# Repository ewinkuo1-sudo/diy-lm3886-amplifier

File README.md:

# LM3886 DIY AB 類立體聲後級

用兩顆 LM3886T 製作**內建電源的雙聲道純後級**，搭配使用者現有的 **Eversolo DAC-Z10（DAC＋前級）**。訊號路徑為 **DAC-Z10 RCA 前級輸出 → 本後級 → 喇叭**，音量與訊源選擇由 Z10 負責。本機採固定增益，前面板規劃電源及狀態指示。

這是第三個獨立擴大機專案，可與 [TPA3255 練習機](https://github.com/ewinkuo1-sudo/diy-tpa3255-amplifier) 及 [Purifi 主力機](https://github.com/ewinkuo1-sudo/diy-purifi-amplifier) 比較架構與製作經驗。

## 目前狀態（2026-10-01 深夜）

- **方向改為「先挑殼、散熱器放殼內、以現有零件重排 PCB＝V0.6」**。機殼改選台灣現貨 **弘宙 102**（型錄 b420 前面板寬、d395 機身寬、c285 深不含把手、e105 高 → 內尺寸估 **393×273×100**，賣家未確認；BZ4312A2 留給下一台）。配置：後排「放大板 L｜電源板｜放大板 R」、前排變壓器居中、左前控制板、右前市電板；散熱器 **150×90×30 鋁擠 ×2 內置兩側**（鰭片朝牆、底板朝板、上蓋底板開通風孔；規格依 8 Ω 連續正弦 θSA ≤1.2 °C/W）。3D 配置：[chassis_102_v06_3d.png](docs/diagrams/chassis_102_v06_3d.png)。下單前問賣家內寬、通風孔、後面板是否空白。
- **2026-10-25 3D 列印機殼 v0.2**：列印機確定為 Bambu Lab H2D，改成底殼一體（298×313×81，內深 305）＋上蓋一片＋市電護罩＋機腳，配置換成兩片現成板（蝦皮 UPC1237 保護器、AC110V 軟啟動板，使用者暫定買）；剛性用格狀梁估算，底板變壓器區肋加高、上蓋肋 13 mm／40 mm 間距後全部過關，散熱片螺絲要墊鋁條。見 [docs/16](docs/16-3D列印機殼v0.2.md)。**未切片、未試印、全是估算。**
- **2026-10-25 另起 3D 列印機殼候選（v0.1）**：使用者買了 176×33×60 散熱片 ×?（蝦皮），評估與模型在 [docs/15](docs/15-3D列印機殼方案.md)：散熱片當左右側牆外露、四周框拆 6 件列印（≤216 mm）、上下蓋建議 2 mm 鋁板；θSA 估約 1.2 °C/W 與原要求同級；材料要 PETG／ASA。**未定案**，弘宙 102 方案照舊保留；圖 `docs/diagrams/chassis_print_v01_*.png`，模型 `mechanical/chassis-print-v01/`。
- **控制／保護板 CTRL 與市電板 MAINS 第一版原理圖＋PCB V0.6 已畫**（2026-10-01 深夜）：CTRL 70×120（UPC1237 保護、7812 輔助電源、G2RL-1-E 喇叭繼電器 ×2、SFH617A 光耦靜音、TL431 旁通計時）、MAINS 70×100（SL22 10005 NTC、K_BYP、K_TRIG）。ERC 0、DRC 0 錯誤，市電／低壓銅箔距離 7.25 mm。繼電器 DC 分斷取 30 VDC 等級（使用者接受）。見 [docs/14](docs/14-V0.4-控制與保護板設計草案.md) 狀態列、[pcb/README「PCB V0.6」](pcb/README.md)。
- **放大板與電源板 V0.6 也畫了（2026-10-02 凌晨，以型錄幾何先畫）**：放大板 **90×80**，U1 用 KiCad 函式庫 TO-220-11 直立封裝、背板貼板邊直接鎖散熱器；電源板 **92×120**，兩欄 381LX、GBJ 朝前、AC 端子朝變壓器、DC 端子朝放大板（snubber 預留位未上板）。**V0.6 五板皆 DRC 0 錯誤**，機箱 3D 已換成真板。IC 幾何、C2 腳距、繼電器腳位到貨要核對。詳見 [pcb/README](pcb/README.md)；V0.5.1／V0.5／V0.4／V0.3 為歷史。**全部仍是工程草稿，不可送製。**
- **放大板與電源板現行為 V0.6.1（2026-10-03 使用者選定併入 main）**：零件、擺位、板尺寸、機殼與散熱器配置與 V0.6 完全相同，只把載流走線加寬到間距規則與鄰近焊盤允許的上限（放大板負電源腳間線 0.5→0.9、電源板主幹 3→5 等），兩板 DRC 0；V0.6 vs V0.6.1 走線電阻對照見 [pcb/README「PCB V0.6.1」](pcb/README.md)。CTRL／MAINS 仍為 V0.6 板檔。
- **目標喇叭 Usher Be-718**（標稱 8 Ω、實測低中音 >6 Ω、約 85 dB）：匹配估算見 [docs/01](docs/01-設計規格.md)；功率／散熱討論以 6–8 Ω 為準。
- **已到貨**：環形變壓器、yosontw 40 件電阻／WIMA／CDE／ROE（2026-09-22）、LM3886T 拆機品 ×4（2026-09-29，T 封裝、NS 打標）。已付 NT$4,821，整機估 10.9k–16.2k（[採購總表 §5](docs/00-採購總表.md)）。
- **2026-10-01 已量變壓器電氣**（採購總表 §1）：標籤 22V 4.2A×2＋12V 1A ≈ **197 VA**；兩組 22V 空載各 22.29 Vac（DCR 0.25／0.2 Ω）、串接 44.6 Vac 同相；12V 12.27 Vac；一次側約 2 Ω；市電 110 V。最壞軌電壓 **±33.5 V**，帶載推估連續 30–32 W／8 Ω。保險絲提案：一次側 T2.5A（有軟啟動）／T3.15A、22V 各 T5A、12V T1.25A。**未量：帶載電壓、絕緣、溫升。**
- **已量零件尺寸**（2026-09-23）：381LX Ø35×50 腳距 10；EKE Ø12×25 腳距 5；EGW 軸向 40×Ø20（V0.5 起改站立封裝，**腳距 15 是假設待實量**）；變壓器 Ø120×約 50、中心孔 Ø40。
- **選型定案**：C 方案雙聲道、雙橋整流、4×10,000µF／63V；47µF＝ROE EGW 無極性、470µF＝ROE EKE／63V；每聲道 30～40W／8Ω 為探索範圍而非額定。
- **本輪可買**：GBJ2510 ×2＋小散熱片＋M3 件、保險絲、機殼（弘宙 102）、散熱器 150×90×30 ×2、控制板零件一套（G2RL-1-E 12VDC ×5、UPC1237 ×2、SL22 10005、SFH617A-3 ×2、TL431、BC327 ×2、7812 等，見採購總表控制板列）；其餘未購件與順序見採購總表 §2／§3。

**要買零件看 [採購總表](docs/00-採購總表.md)**（已買／未買兩張表＋購買順序）。**要接手看 [HANDOFF.md](HANDOFF.md)**。**歷史逐日紀錄看 [CHANGELOG.md](CHANGELOG.md)**。

## 系統方塊

```mermaid
flowchart LR
    PRE[DAC-Z10\nDAC＋前級／音量控制]
    subgraph AMP[LM3886 純後級機殼]
        IN[RCA 輸入] --> C[兩顆 LM3886T 功率級]
        C --> D[輸出穩定網路]
        D --> REL[喇叭保護／繼電器\nCTRL 板 V0.6 草稿]
        AC[AC 入口／保險絲／開關] --> SS[軟啟動 NTC＋旁通\nMAINS 板 V0.6 草稿]
        SS --> T[隔離環形變壓器]
        T --> PSU[雙橋整流／濾波]
        PSU --> C
        CTRL[UPC1237 啟停／DC 偵測\nCTRL 板 V0.6 草稿] -. 控制 .-> C
        CTRL -. 控制 .-> REL
    end
    PRE --> IN
    REL --> SPK[喇叭]
```

## 設計重點

| 項目 | 目前選擇／待驗證 |
|---|---|
| 功率級 | LM3886T ×2，非橋接、非並聯；已訂拆機品，/NOPB 未確認 |
| 輸出目標 | 每聲道約 30～40W／8Ω 探索範圍，額定待實測 |
| 電源 | 已訂雙 22Vac＋單 12Vac；雙橋架構保留，約 ±30V 等級；VA／電流／最大電壓待確認 |
| 增益 | IC 中頻閉迴路 21 倍；含輸入串阻後約 20.09 倍 |
| 輸入 | DAC-Z10 RCA 前級輸出；後級 40W 約需 0.89Vrms，音量由 Z10 控制 |
| 靜音／保護 | 放大板保留測試跳線；CTRL 板 V0.6 草稿以 UPC1237 做 DC 偵測、開機延遲、掉電快斷，光耦接管 JP1 靜音，解除靜音＝喇叭繼電器吸合 |
| 散熱 | T 封裝，**2026-10-01 改以 8 Ω 連續正弦為準：每聲道散熱器 ≤1.2 °C/W**（6 Ω 正弦需 ≤0.65）、介面 ≤0.3 °C/W；選 150×90×30 鋁擠內置兩側，估法 θSA≈1000／表面積(cm²)；原 0.4 °C/W 是 ±41 V 前提的保守值 |
| 本版負載 | 8Ω 非感性假負載；目標喇叭 Usher Be-718（標稱 8Ω、低中音實測 >6Ω、靈敏度實測約 85dB），匹配估算見 [01](docs/01-設計規格.md)「目標喇叭」節；真實喇叭需另外驗證 |

TI 列出 ±35V、8Ω 下 50W 的元件性能條件；這不是本機實測規格。[原廠資料](https://www.ti.com/product/LM3886)

## 文件

| 文件 | 內容 |
|---|---|
| [採購總表](docs/00-採購總表.md) | **採購單一入口**：已買／未買、購買順序、商品連結 |
| [設計規格](docs/01-設計規格.md) | 電路、接地、Z10 介面與保護邊界 |
| [功率與散熱估算](docs/02-功率與散熱估算.md) | 可重算的數字、公式與假設 |
| [上電與驗收](docs/04-上電與驗收.md) | 從低電壓到雙聲道功率測試 |
| [內建電源與機構](docs/05-內建電源與機構.md) | 變壓器、整流、接地、機殼分區與電源估算 |
| [喇叭保護與啟停設計計畫](docs/13-喇叭保護與啟停設計計畫.md) | V0.4 需求：保護、延遲、DC 偵測與啟停方案 |
| [V0.4 控制與保護板設計草案](docs/14-V0.4-控制與保護板設計草案.md) | 控制板架構、啟停時序、與現有板介面、繼電器篩選、軟啟動與輔助電源計算；開頭狀態列記 2026-10-01 的選型決定與原理圖／PCB V0.6 偏離之處 |
| [控制板原理圖 CTRL](electrical/preview/control-v01.png)／[市電板 MAINS](electrical/preview/mains-v01.png) | 2026-10-01 第一版（生成器 `tools/build_control_board.py`，ERC 0）；[CTRL PDF](electrical/preview/control-v01.pdf)、[MAINS PDF](electrical/preview/mains-v01.pdf) |
| [導讀圖索引](docs/diagrams/README.md) | 單聲道完整接線圖（放大板＋電源板全部畫出）與五張中文導讀圖 |
| [BOM 草案](electrical/bom-draft.csv) | 由 KiCad netlist 匯出，含選型條件 |
| [驗證紀錄](electrical/validation.md) | ERC、網路核對與未驗證事項 |
| [原理圖說明](electrical/README.md) | 放大板與電源次級 KiCad 圖、看圖與重建方式 |
| [PCB](pcb/README.md) | **現行五板：放大板 V0.6.1 90×80 ×2、電源板 V0.6.1 92×120（V0.6 擺位＋加寬走線）、CTRL V0.6 70×120、MAINS V0.6 70×100，皆 DRC 0**；V0.6 放大板／電源板、V0.5.1／V0.5／V0.4／V0.3 歷史：板檔、DRC、審查結論與載流計算表 |
| [機箱 3D 配置](docs/diagrams/chassis_102_v06_3d.png) | 弘宙 102 內部等角＋俯視（`tools/draw_chassis_scene_v06.py`，pyvista；CTRL／MAINS 為真板 3D，放大板與電源板為 V0.6 目標外形示意） |
| [PCB 看圖資料](pcb/inspection-v051/README.md) | V0.5.1（放大板 D＋電源板）正反面銅箔、組裝、3D 預覽與零件核對表；[V0.5](pcb/inspection-v05/README.md)／[V0.4](pcb/inspection-v04/README.md)／[V0.3](pcb/inspection-v03/README.md) 版保留 |
| [工具說明](tools/README.md) | 各腳本用途與執行順序 |
| [接班進度](HANDOFF.md) | 現況與下一階段工作 |
| [變更紀錄](CHANGELOG.md) | 逐日進度歷史 |

## 電路圖與 PCB 預覽

[放大板 PDF](electrical/preview/lm3886-v01.pdf) · [KiCad 原理圖](electrical/lm3886-v01.kicad_sch)

[電源 PDF](electrical/preview/internal-psu-v02.pdf) · [電源 BOM](electrical/psu-bom-draft.csv)

## 重建與下一步

需要 Python 3、KiCad 10 CLI、Poppler 的 `pdftoppm`，Python 無第三方套件需求：

```sh
python3 tools/rebuild.py
```

`rebuild.py` 目前只重建放大板與電源次級原理圖；控制板與市電板（`tools/build_control_board.py`）和所有 PCB 腳本要手動跑，順序見 [tools/README](tools/README.md)。

下一步（詳見 [HANDOFF](HANDOFF.md)）：量 LM3886T 三個尺寸、問賣家弘宙 102 內寬 → 必要時修正 V0.6.1 放大板的 U1 位置；審控制板原理圖與 PCB、買控制板零件並核對繼電器腳位；麵包板實測 UPC1237 在 12 V 供電下的門檻與延遲；變壓器帶載量測。放大板單獨驗證時仍可用限流實驗電源；成機供電採內建方案。

PDF 重製：先執行 `python3 tools/rebuild.py`，再以安裝 reportlab／pypdf 的 Python 執行 `tools/build_project_pdf.py`；非 Windows 環境需設定 `LM3886_FONT` 指向 CJK TrueType 字型。產物在 `output/`，不入版控。

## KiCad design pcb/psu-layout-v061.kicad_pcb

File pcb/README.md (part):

# PCB

**現行版本：放大板與電源板 V0.6.1（2026-10-03 使用者選定併入 main，V0.6 擺位不動、載流走線加寬，見「PCB V0.6.1」節），CTRL／MAINS V0.6。** V0.6 放大板／電源板自同日起為歷史（板檔保留）。**V0.5.1 自 2026-10-02 起為歷史**（2026-10-01 使用者選定併入 main：電源板的整流橋改為 GBJ2510 直立上板，取代 KBPC2510 鎖機殼＋Faston 線；放大板 D 90×90 與 V0.5 相同），兩板 KiCad 10.0.6 DRC 0 違規、0 未連通，見下方「PCB V0.5.1」節；正反面銅箔、組裝極性、3D 預覽與零件核對表在 [inspection-v051](inspection-v051/README.md)。**V0.5 電源板（`psu-layout-v05`）自 2026-10-01 起為歷史**，板檔與 [inspection-v05](inspection-v05/README.md) 保留。**V0.4 自 2026-09-29 起為歷史版本**（放大板 D／C 與電源板板檔、DRC、[inspection-v04](inspection-v04/README.md) 保留）。**V0.3 自 2026-09-24 起為歷史版本**：板檔、DRC、雜湊綁定與審查結論原樣保留供對照，不再修改。

---

## PCB V0.3（B 方案，歷史版本）

**兩片 100×90 mm 單聲道放大板＋一片 160×120 mm 共用電源板。**（2026-09-24 放大板已改為 **115×90 mm** 並重建，DRC 0 違規、0 未連通。）

> ⚠️ **工程草稿，不可送製。** 兩板在 KiCad 10.0.6 下 0 DRC 違規、0 未連通，54＋35 焊盤網路與原理圖相符；但封裝是暫定外框與假設高度，溫升、散熱、機構與線束都沒驗證，**沒有 Gerber**。DRC 與中心線幾何不代表高頻穩定、載流溫升或製造條件已驗證。

| 項目 | 單聲道板 ×2 | 電源板 ×1 |
|---|---|---|
| 可編輯 PCB | [mono-layout-v03.kicad_pcb](mono-layout-v03.kicad_pcb) | [psu-layout-v03.kicad_pcb](psu-layout-v03.kicad_pcb) |
| 專案規則 | [KiCad 專案](mono-layout-v03.kicad_pro) | [KiCad 專案](psu-layout-v03.kicad_pro) |
| 圖面 | [PNG](preview/mono-layout-v03.png)／[原生 SVG](preview/mono-v03-native.svg) | [PNG](preview/psu-layout-v03.png)／[原生 SVG](preview/psu-v03-native.svg) |
| 封裝假設 | [清單](mono-layout-v03-footprints.csv) | [清單](psu-layout-v03-footprints.csv) |
| 原生 DRC | [0 違規、0 未連通](mono-v03-drc.json) | [0 違規、0 未連通](psu-v03-drc.json) |

其他資料：[銅箔計算表](current-budget-v03.md)／[完整計算資料與輸入雜湊](current-budget-v03.json)、[驗證摘要](validation-v03.json)、[DRC 檔案綁定](drc-provenance-v03.json)、[正反面／組裝／3D 看圖資料](inspection-v03/README.md)、[零件與封裝核對表](inspection-v03/parts-audit.md)、[左右聲道對照](mono-channel-mapping.csv)。

V0.1／V0.2 板檔、封裝庫與舊腳本已於 2026-09-21 刪除，從 Git 歷史（`41b217c`）取回；僅保留 `archive/v02/*-layout-v02.json` 供 `analyze_pcb_v03.py` 做 V0.2→V0.3 對照。

## PCB V0.4 放大板・變體 C（改良星型接地，2026-09-24 晚）

> ⚠️ **工程草稿，不可送製。** 電路、零件與封裝外框全部沿用 V0.3；只改零件位置與銅箔。KiCad 10.0.6 下 **0 DRC 違規、0 未連通**，54 焊盤網路與原理圖相符，接地分路檢查通過（[validation-v04.json](validation-v04.json)）。變體 D 與電源板 V0.4 見後兩節；**使用者 2026-09-24 選定 D 為主，C 保留備查**。

| 項目 | 檔案 |
|---|---|
| 可編輯 PCB／專案 | [mono-layout-v04c.kicad_pcb](mono-layout-v04c.kicad_pcb)／[.kicad_pro](mono-layout-v04c.kicad_pro) |
| 位置與逐段走線定義 | [tools/pcb_layout_v04.py](../tools/pcb_layout_v04.py)（生成器 [build_pcb_v04.py](../tools/build_pcb_v04.py) 沿用 V0.3 封裝庫與 `build()`） |
| 原生 DRC／驗證 | [mono-v04c-drc.json](mono-v04c-drc.json)／[validation-v04.json](validation-v04.json)（`verify_pcb_v04.py`，匯合半徑 5 mm，V0.3 為 4 mm） |
| 走線資料／封裝清單 | [mono-layout-v04c.json](mono-layout-v04c.json)／[footprints.csv](mono-layout-v04c-footprints.csv) |

**改了什麼（對應 2026-09-24 審 V0.3 的七點中屬於放大板的五點）：**

1. 100n 旁路貼 IC 腳：C3 (45.8,19) 跨 pin 5 (V+)–pin 7 (GND)，C4 (50.8,24.5) 跨 pin 4 (V-)–pin 7；V- 從 pin 3／pin 5 之間以 0.5 mm 底層線直下 pin 4（IC 腳間隙 1.4 mm 只容得下這個寬度，是全板最窄處）。
2. 470µF C7 (36,34.5)／C6 (54,34.5) 上移到 IC 正下方，**STAR (50.8,34.5) 就是兩顆之間 9 mm 長的接地條**；J5 留板底，GND 以 3 mm 底層線沿 x=50.8 直上 STAR。
3. J1 訊號與接地並排走到 C1／R1／R2 角落，R1.1 與 R2.1 相鄰 3 mm 形成訊號地 SG (71.5,14.5)，再一條 0.8 mm 底層線回 STAR；C2 與 C8 的接地併入這條訊號地分路（靜音電容只有 mA 級，不再另走一路）。
4. Zobel C5 移到 (55,45)，接地 1.0 mm 直入 STAR；R5 輸出端接到輸出主幹的轉折點 (22,43.5)。
5. C2 改平放在右半 (112,53)，C2.2 靠 R3.1；R8／C8／JP1 移到右下角。**4 個過孔全部取消**（V0.3 有 3 個），每個網路都在單層走完或用零件焊盤換層。

| 銅箔中心線長度（mm） | V0.3 | V0.4 C |
|---|---:|---:|
| C3 接地端→U1.7 | 24.2 | **5.2** |
| C4 接地端→U1.7 | 33.2 | **10.7** |
| C3 旁路迴路（U1.5→C3.1＋C3.2→U1.7） | 43.6 | **10.2** |
| C4 旁路迴路（U1.4→C4.2＋C4.1→U1.7） | 50.2 | **27.0** |
| C6 接地端→STAR | 16.5 | **3.2** |
| C7 接地端→STAR | 11.5 | 9.8 |
| Zobel C5 接地端→STAR | 72.1 | **11.5** |
| J1 接地→STAR（訊號地） | 64.6 | 76.5 |
| C2 接地→STAR（訊號地） | 69.7 | 107.1 |
| J5 接地→STAR | 27.4 | 42.5 |
| U1.3→L1.1 輸出主幹 | 48.8 | 50.2 |
| U1.3→R4.2 回授取樣線 | 7.1 | **50.4** |
| U1.9→R4.1（-IN） | 5.5 | 12.5 |

粗體是本輪目標項。**代價**（有意為之、可再議）：回授取樣線改由 pin 3 向上穿過 pin 2／pin 4 之間，沿 IC 本體下方（y=4.3，底層）繞到右側 R4，長 50 mm——它是低阻抗的輸出取樣，長度本身影響小，但與 -IN 線的 12.5 mm 一起，比 V0.3 多暴露在 IC 附近；訊號地與 J5 回流變長是把 STAR 上移到 IC 下方的直接結果。這些都是中心線幾何，**不代表失真或穩定度已改善**，要等實板量。

**還沒做：** 變體 D（同位置、底層整面 GND 鋪銅取代分支；`verify` 的分路檢查對 D 要跳過）、電源板 V0.4（原理圖已加 J204／snubber，PCB 未畫）、V0.4 的 `current-budget`／`analyze` 對照、3D 與導讀圖。V0.3 板檔與雜湊全部未動。

### 變體 D（底層整面接地，2026-09-24 深夜）

零件位置、訊號與電源銅箔與變體 C **完全相同**；只把 C 的全部 GND 分路線拿掉，改成一整片底層 GND 鋪銅（`AMP_D`，間距 0.3、最小寬 0.35、焊盤熱阻隔 spoke 0.8／gap 0.5）。KiCad 10.0.6 **0 DRC 違規、0 未連通**，鋪銅填完只有一個連通區（沒有孤島）；`verify_pcb_v04.py` 對 D 跳過分路檢查，只核對焊盤網路與鋪銅連通區數。

| 項目 | 檔案 |
|---|---|
| 可編輯 PCB／專案 | [mono-layout-v04d.kicad_pcb](mono-layout-v04d.kicad_pcb)／[.kicad_pro](mono-layout-v04d.kicad_pro) |
| 原生 DRC／走線＋鋪銅資料 | [mono-v04d-drc.json](mono-v04d-drc.json)／[mono-layout-v04d.json](mono-layout-v04d.json)（含填銅多邊形） |

**2026-09-24 使用者決定：以 D 為主、C 保留。** 隨即修掉 D 的缺點：3 mm 輸出主幹（pin 3→L1）與 Zobel 接主幹的線改走**頂層**，C7→pin 1 的 V+ 進線改走底層（只在 x=36 切一道 20 mm 的短縫），原本多給 C3.1 的一條 V+ 分支拿掉（C3.1 由 pin 1→pin 5 連線供電）。修後底層鋪銅仍是單一連通區，板左半改由 C7 下方整片相連，不再只靠窄帶；DRC 0 違規、0 未連通。C 與 D 的取捨（星型分路 vs 整面低阻抗回流）沒有實測前不能說哪個一定好，所以 C 的板檔照樣留著。

### 電源板 V0.4（每聲道端子＋snubber 預留，2026-09-24 深夜）

AC 進線、保險絲、橋堆端子、四顆 10,000µF、洩放電阻的位置與 V0.3 相同，對應 2026-09-24 審查的第 5、6 點：

- **J203（左聲道）／J204（右聲道）各一組 3P 端子**在右板邊 (151,42)／(151,66)。STAR 移到 (138,59.08)，C202／C204 的接地各一條 4 mm 底層線斜入 STAR，再各一條 4 mm 線到兩個端子的 G 腳；V+ 走頂層 x=145 到 J203 再沿板邊 x=157 到 J204，V- 走頂層 x=145 從底部上來分別接兩個端子。C205／C206 100n 貼在 STAR 旁。
- **每繞組一組 snubber 預留位**（Cx‖(Rs+Cs)）排在橋堆端子下方一列：C207／C208／R203 在 y=53，C209／C210／R204 在 y=113。接在保險絲**前**的繞組兩端（J201／J202 那一側），1 mm 細線；Cx、Cs 用 `Film_P15`、Rs 用 `R_2W_P20` 暫代，**只留孔不填料**，等變壓器實測振鈴再決定值與是否裝。
- KiCad 10.0.6 **0 DRC 違規、0 未連通**，50 焊盤網路與 V0.4 電源原理圖相符（[psu-v04-drc.json](psu-v04-drc.json)、[validation-v04.json](validation-v04.json)）。負半邊的 snubber 回線原本與 V- 充電線（4 mm）重疊 0.2 mm，改到 y=110.6 後通過。

| 項目 | 檔案 |
|---|---|
| 可編輯 PCB／專案 | [psu-layout-v04.kicad_pcb](psu-layout-v04.kicad_pcb)／[.kicad_pro](psu-layout-v04.kicad_pro) |
| 位置與走線定義 | [tools/pcb_layout_v04_psu.py](../tools/pcb_layout_v04_psu.py) |
| 原生 DRC／走線資料／封裝清單 | [psu-v04-drc.json](psu-v04-drc.json)／[psu-layout-v04.json](psu-layout-v04.json)／[footprints.csv](psu-layout-v04-footprints.csv) |

**V0.4 三塊板都畫完了（放大板 C、放大板 D、電源板）**，等使用者看圖選 C 或 D。之後才做：V0.4 的 `current-budget`／`analyze` 對照、3D 與導讀圖、系統並排圖；V0.3 檔案與雜湊全部未動。

## PCB V0.6.1（2026-10-03，現行：放大板與電源板）

**V0.6.1 = V0.6 放大板與電源板，零件、位置、網路、板尺寸、機殼（弘宙 102）與散熱器（150×90×30 內置）全部不動，只把載流路徑的銅箔加寬到 0.3 mm 間距規則與鄰近焊盤允許的上限。** CTRL／MAINS 不在此版（沿用 V0.6）。兩板 KiCad 10.0.6 DRC **0 錯誤、0 未連通**，[validation-v061.json](validation-v061.json) 通過（同 V0.6 的檢查：焊盤網路、IC 背板貼邊、GBJ 散熱片包絡、鋪銅單一連通區）。

**改了什麼（寬度 mm，V0.6→V0.6.1）**

| 板 | 走線 | V0.6 | V0.6.1 | 限制來源 |
|---|---|---:|---:|---|
| 放大板 | 負電源腳間線 C4→U1 腳 4（從腳 3／5 之間下去） | 0.5 | **0.9** | 焊盤 1.8、同排腳距 3.4 → 最多 1.0；腳 3 的輸出短線同時縮到 1.8（＝焊盤直徑）才能各留 0.3 |
| 放大板 | 腳 1／5 V+ 底層短線（兩排腳之間） | 1.0 | 2.0 | 兩排腳間隙 5.08 扣焊盤 |
| 放大板 | 470 µF→IC：C7→腳 1（底層）／C6→C4（頂層） | 2.0／1.5 | 3.0／2.5 | — |
| 放大板 | 電源饋線 J5→C7／J5→C6 | 3.0／3.0 | 4.0／**3.5** | 負饋線 x=58 夾在 C5（x=55）與 C2.2（x=62）之間，4.0 會碰 C2.2 |
| 放大板 | 輸出主幹 腳 3→L1：短線／立段／主幹 | 2.0／2.5／3.0 | 1.8／3.0／4.0 | 主幹兩個轉折點各往左上移 0.6（(34,31.5)→(33.4,30.9)、(22,43.5)→(21.4,42.9)）避開 4.0 的 VCC 饋線；Zobel 饋線改接到新頂點 |
| 放大板 | L1→R7、L1→J2 喇叭線 | 1.5／3.0 | 3.0／4.0 | — |
| 電源板 | 正負軌、地、AC 主幹 | 3.0 | 5.0 | — |
| 電源板 | VEE 輸出（頂層 y=26、底層 y=24.5） | 2.5 | 4.0 | — |
| 電源板 | AC 回線（−）J202→BR2 | 2.0 | 4.0 | 原本是唯一比同類細的一段 |
| 電源板 | GND 星點連線 y=78 | 3.0 | 4.0 | 5.0 會離 R202.2 焊盤只剩 0.30 |
| 電源板 | 進 3P 端子的地線末段、J201.2→(13.5,110) | 3.0 | 3.0 | 端子焊盤 3.0、腳距 5.08，寬線進焊盤會碰隔壁腳；首輪 DRC 抓到 POS_AC2 的 5.0 端蓋壓到 J201.1，改從 y=110 起寬 |

訊號、回授、靜音、Zobel、洩放與 100 nF 旁路的細線不動（不載負載電流）。回授取樣線長度 35.5 mm、反相輸入線 16.5 mm 與 V0.6 相同；安靜線對電源線的投影最小邊距由 2.33 降到 2.08 mm（L_FB_AC 對 VEE 饋線，頂層同層），對負載線由 9.03 升到 9.13 mm。

**走線電阻對照**（`tools/analyze_pcb_v061.py` → [current-budget-v061.json](current-budget-v061.json)；1 oz／25 °C，±30 V、每聲道 40 W／8 Ω 正弦為尺寸計算點、靜態 85 mA、充電脈衝 15 % 導通；只算銅箔中心線，不含焊盤、孔壁、焊點、接頭、線材、ESR 與電感，**不是溫升預測**）

| 路徑 | 長度 mm | 最窄 V0.6→V0.6.1 | R V0.6 mΩ | R V0.6.1 mΩ | 變化 | 峰值 A | 峰值壓降 V0.6.1 mV | 發熱 V0.6.1 mW |
|---|---:|---:|---:|---:|---:|---:|---:|---:|
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
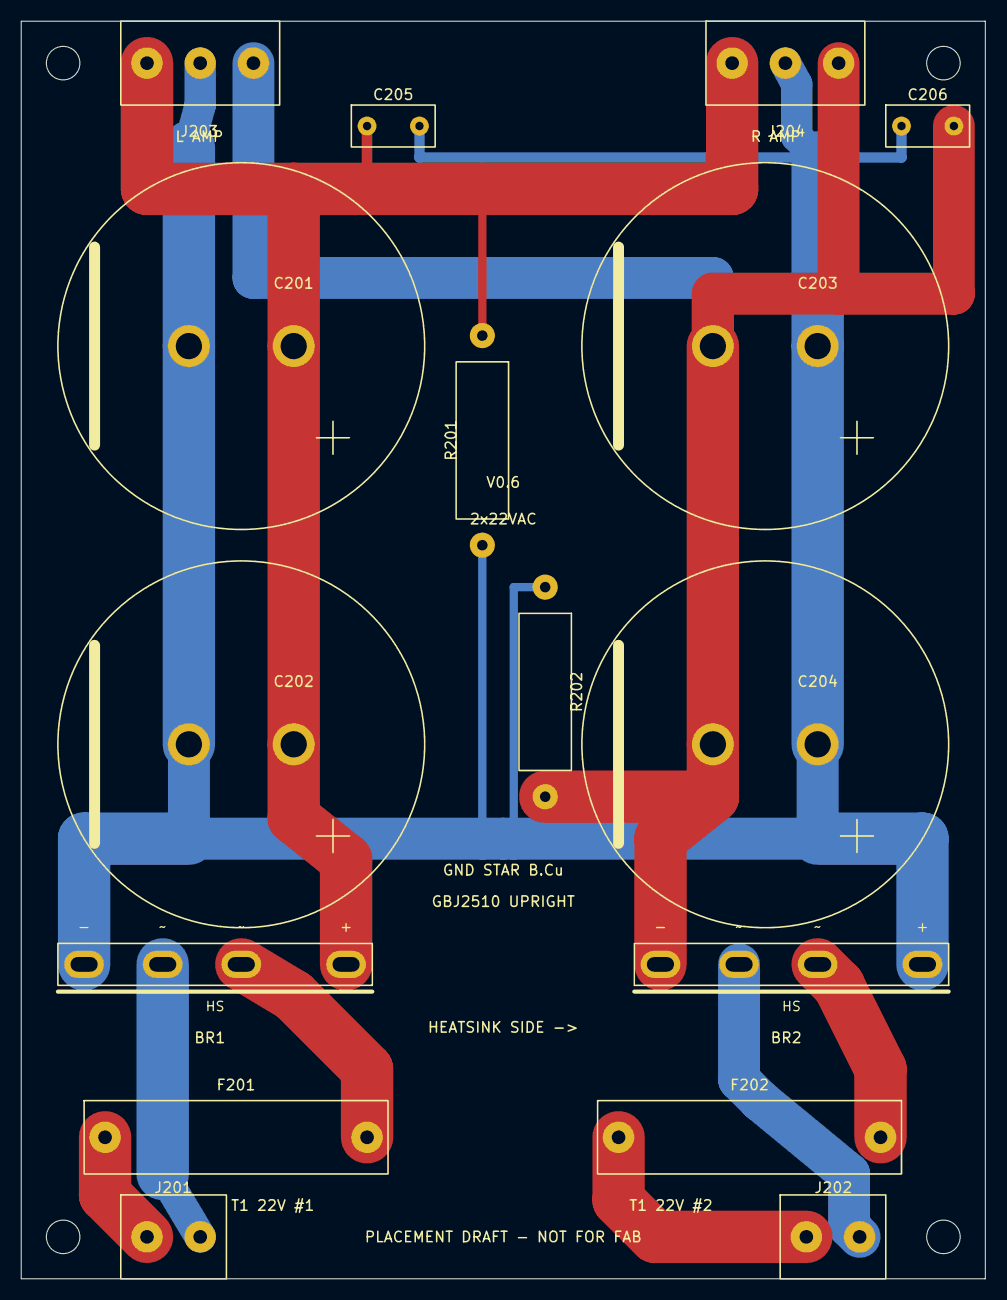
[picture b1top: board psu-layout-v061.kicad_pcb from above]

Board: 2 copper layers, 92.0 x 120.0 mm, 20 parts (0 on the bottom side), 9 nets.

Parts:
BR1, BR2: >=15A / >=200V TBD; GBJ_Upright_P10_7.5_7.5
C201, C202, C203, C204: 10000u / 63V; CP_D35_P10
C205, C206: 100n / 100V film; Film_P5
F201, F202: TBD per transformer; Fuse5x20_P25
H1, H2, H3, H4: M3 provisional
J201: T1 SEC 1; Terminal2_P5.08
J202: T1 SEC 2; Terminal2_P5.08
J203: TO L AMP J5; Terminal3_P5.08
J204: TO R AMP J5; Terminal3_P5.08
R201, R202: 2.2k / 2W BLEED; R_2W_P20

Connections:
GND: BR1.N, BR2.P, C201.2, C202.2, C203.1, C204.1, C205.2, C206.1, J203.2, J204.2, R201.2, R202.1
NEG_AC1: F202.1, J202.1
NEG_AC2: BR2.AC2, J202.2
NEG_AC_FUSED: BR2.AC1, F202.2
POS_AC1: F201.1, J201.1
POS_AC2: BR1.AC2, J201.2
POS_AC_FUSED: BR1.AC1, F201.2
VCC: BR1.P, C201.1, C202.1, C205.1, J203.1, J204.1, R201.1
VEE: BR2.N, C203.2, C204.2, C206.2, J203.3, J204.3, R202.2

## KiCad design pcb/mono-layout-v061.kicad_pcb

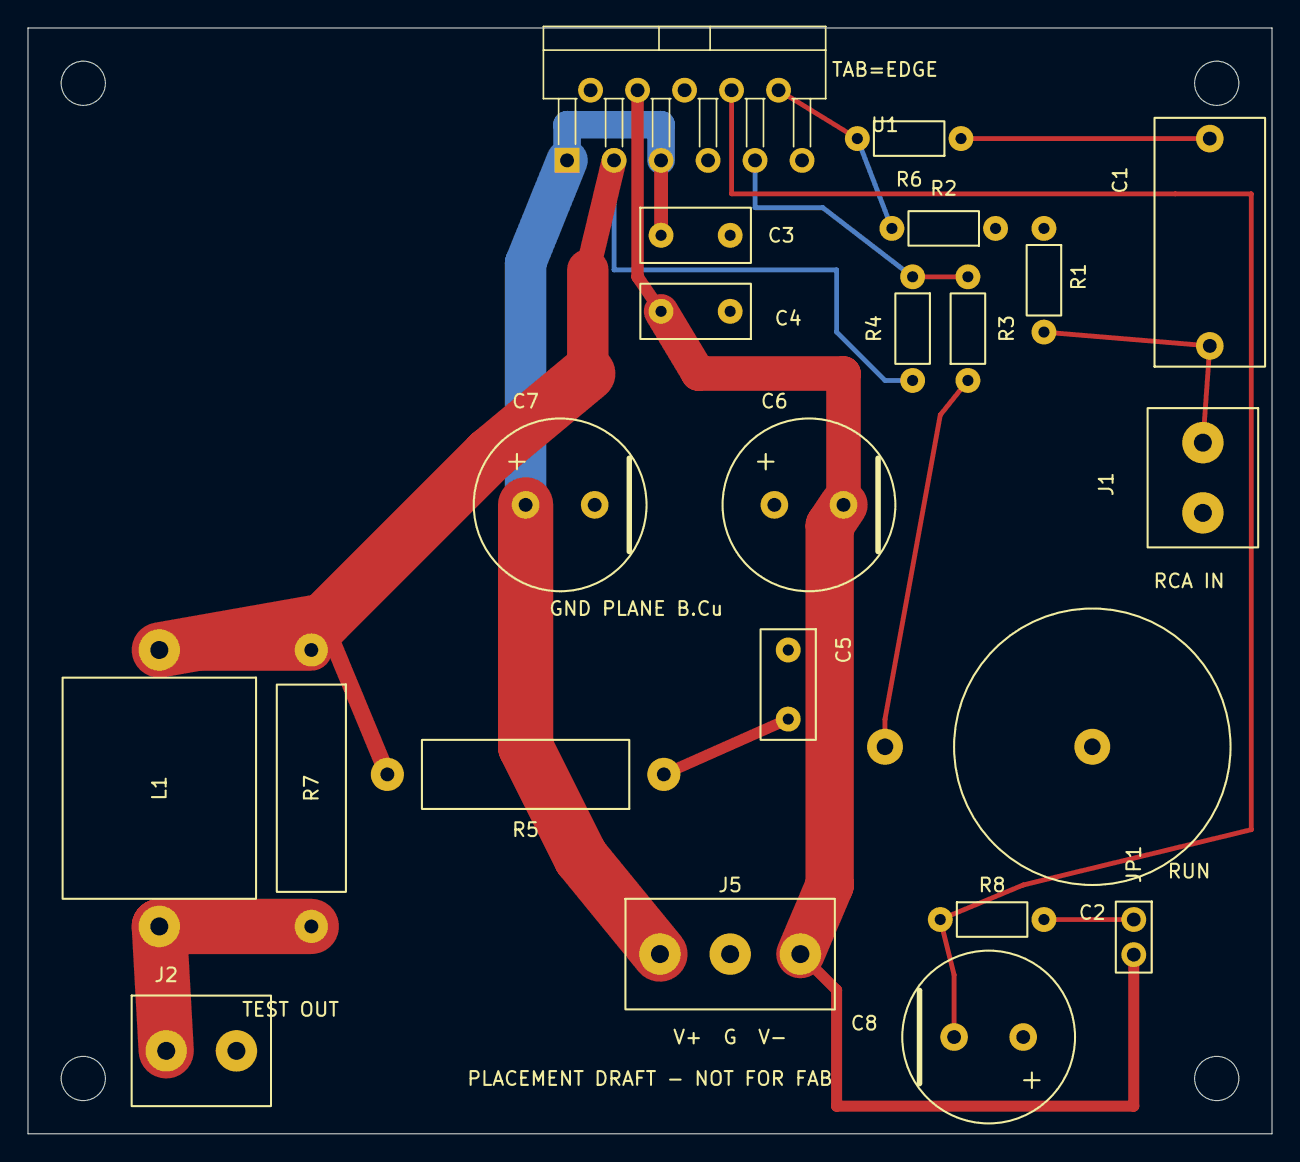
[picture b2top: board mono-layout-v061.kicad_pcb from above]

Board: 2 copper layers, 90.0 x 80.0 mm, 26 parts (0 on the bottom side), 13 nets.

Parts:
C1: 2.2u / 100V film; Film_P15
C2: 47u / 63V BP; BP_Axial_Vert_D20_P15
C3, C4: 100n / 100V; Film_P5
C5: 100n / 100V film; Film_P5
C6, C7: 470u / 63V; CP_D12.5_P5
C8: 100u / 100V; CP_D12.5_P5
H1, H2, H3, H4: M3 provisional
J1: L RCA; Terminal2_P5.08
J2: L TEST OUT; Terminal2_P5.08
J5: INTERNAL PSU; Terminal3_P5.08
JP1: L RUN LINK; Header2_P2.54
L1: 0.7uH / air core; AirCoil_P20
R1: 1M; R_P7.5
R2: 22k; R_P7.5
R3: 1k / 1%; R_P7.5
R4: 20k / 1%; R_P7.5
R5: 2.7R / 2W; R_2W_P20
R6: 1k; R_P7.5
R7: 10R / 2W; R_2W_P20
R8: 22k / 0.6W; R_P7.5
U1: LM3886T; LM3886T_TO220-11

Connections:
GND: C2.1, C3.2, C4.1, C5.1, C6.1, C7.2, C8.1, J1.2, J2.2, J5.2, R1.1, R2.1, U1.7
L_AC: C1.2, R6.1
L_FB_AC: C2.2, R3.1
L_IN: C1.1, J1.1, R1.2
L_INV: R3.2, R4.1, U1.9
L_MUTE: C8.2, R8.1, U1.8
L_OUT: L1.1, R4.2, R5.2, R7.1, U1.3
L_PLUS: R2.2, R6.2, U1.10
L_RUN: JP1.1, R8.2
L_SPK: J2.1, L1.2, R7.2
L_ZOBEL: C5.2, R5.1
VCC: C3.1, C7.1, J5.1, U1.1, U1.5
VEE: C4.2, C6.2, J5.3, JP1.2, U1.4

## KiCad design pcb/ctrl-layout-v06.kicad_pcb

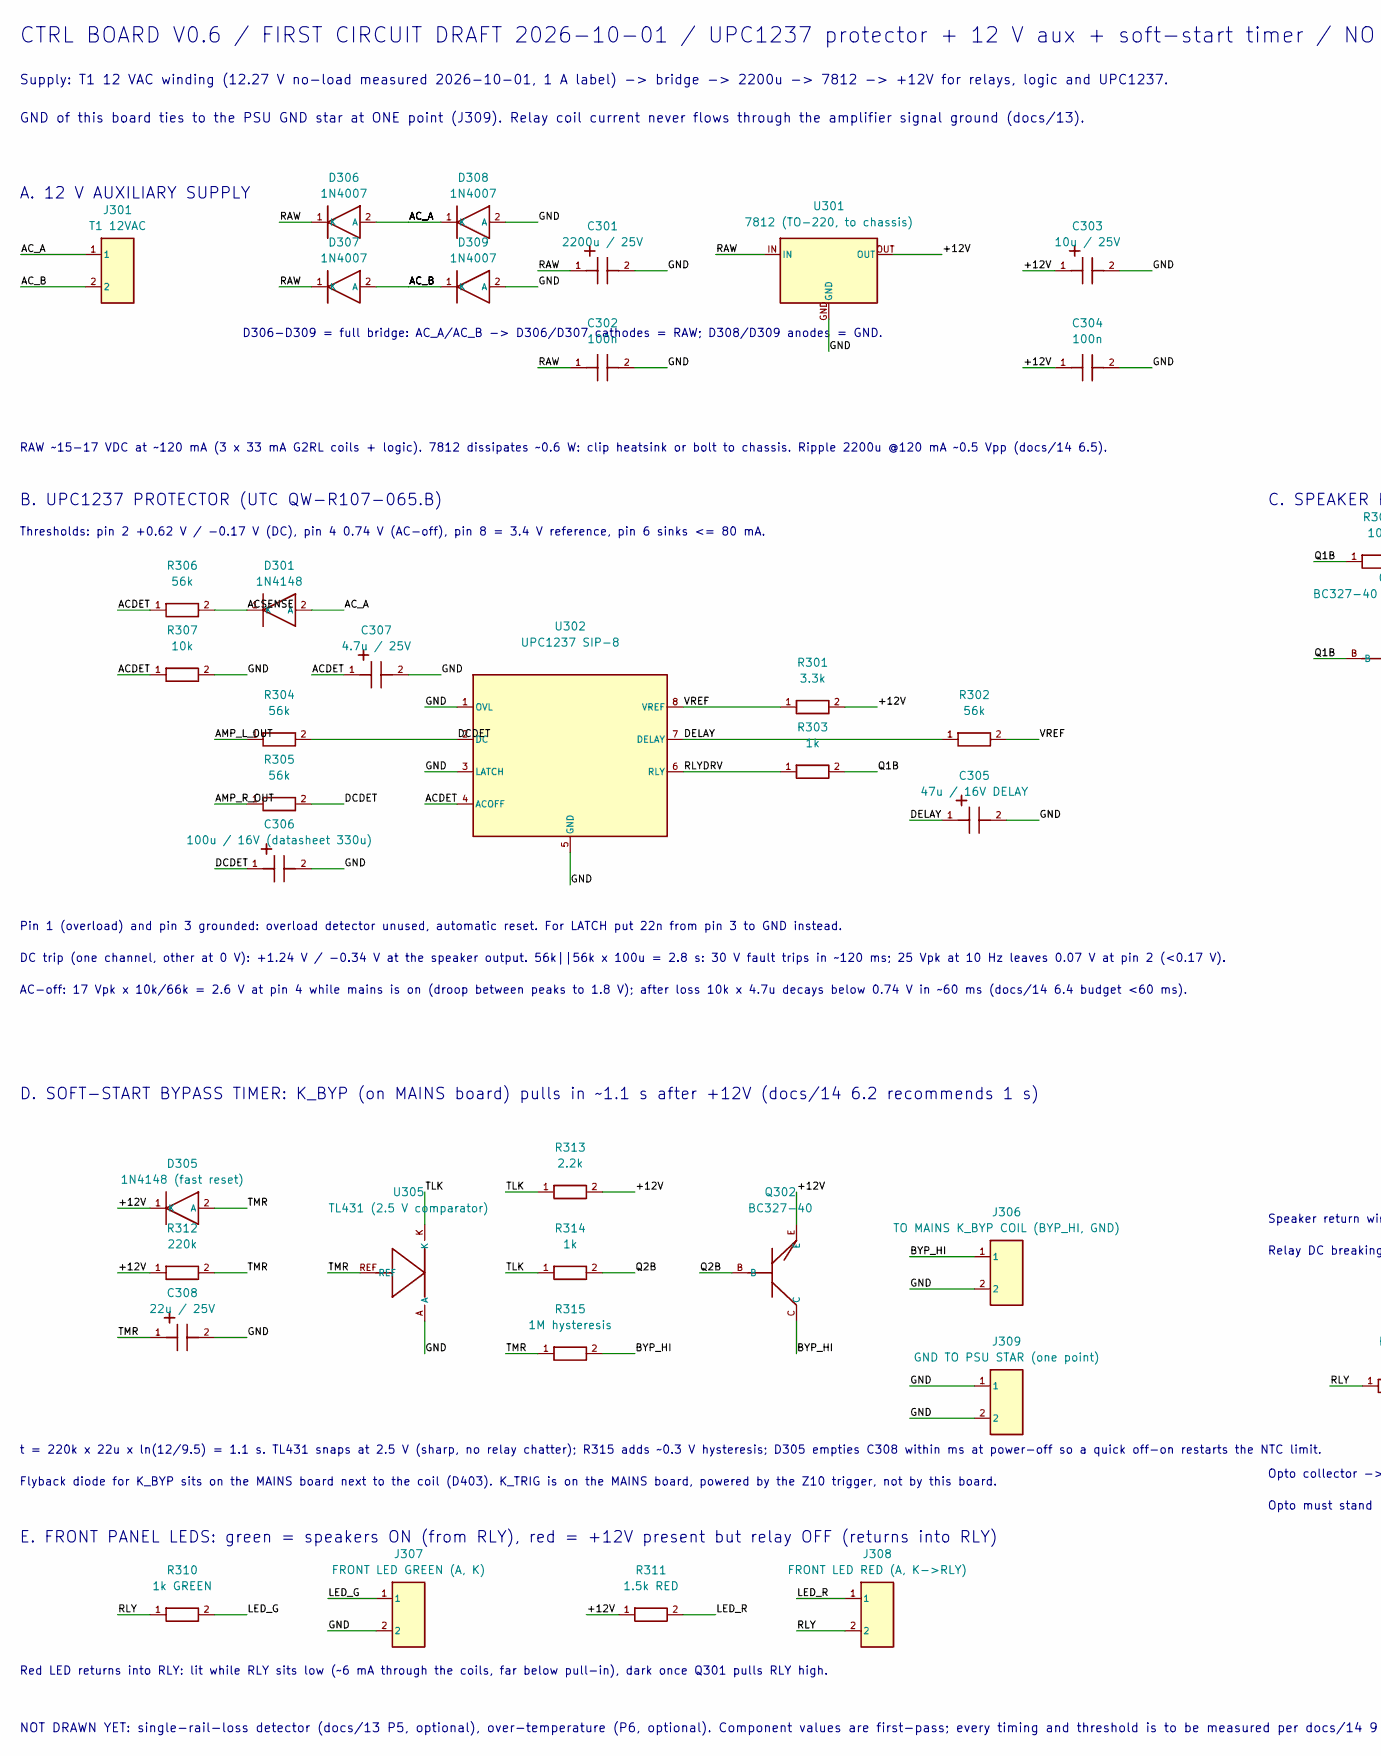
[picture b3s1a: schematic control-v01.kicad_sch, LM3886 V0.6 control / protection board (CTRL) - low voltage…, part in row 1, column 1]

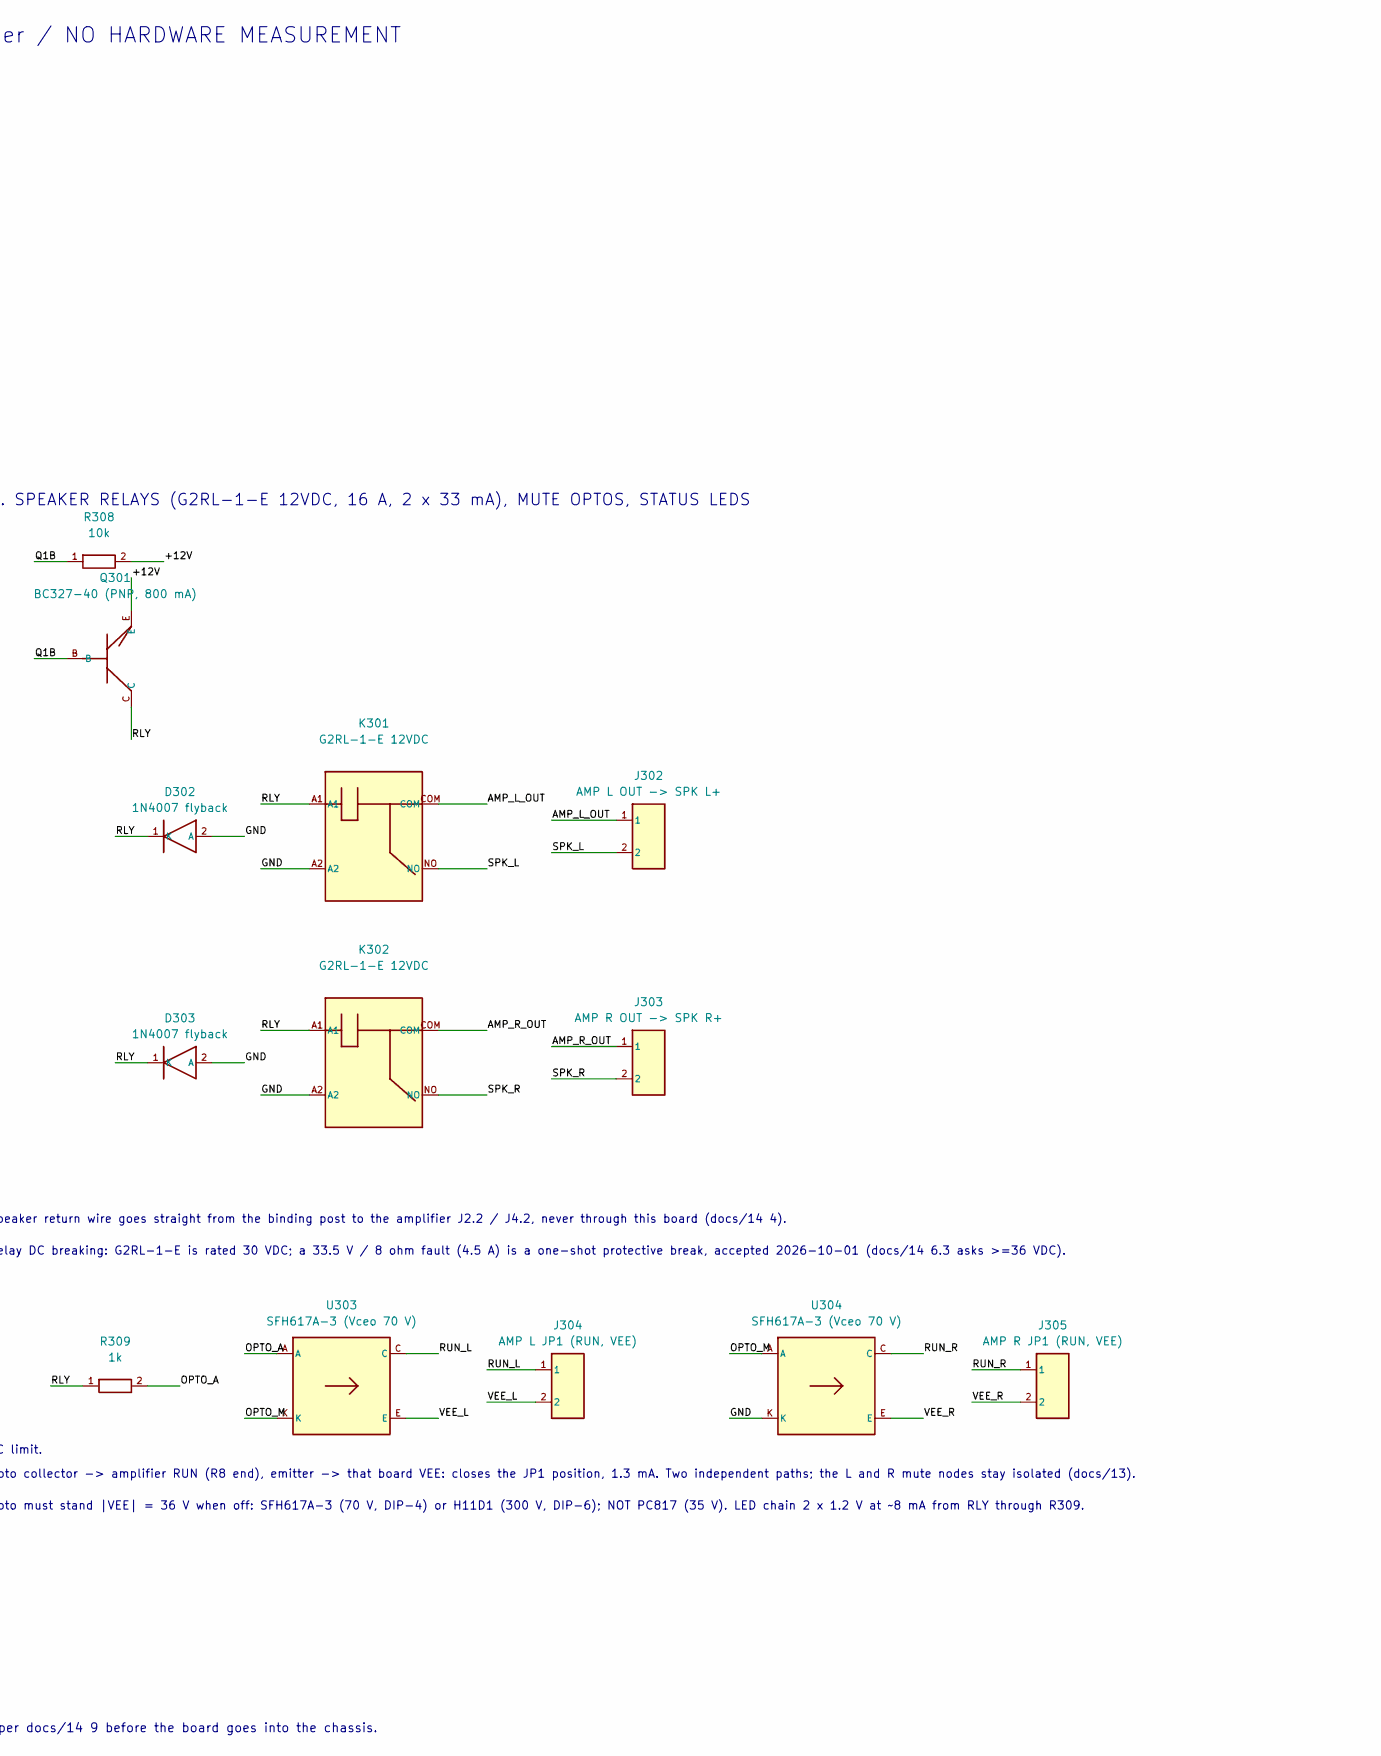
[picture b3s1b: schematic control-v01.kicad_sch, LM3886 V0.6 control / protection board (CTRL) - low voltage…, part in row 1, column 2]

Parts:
C301: 2200u / 25V
C302, C304: 100n
C303: 10u / 25V
C305: 47u / 16V DELAY
C306: 100u / 16V (datasheet 330u)
C307: 4.7u / 25V
C308: 22u / 25V
D301: 1N4148
D302, D303: 1N4007 flyback
D305: 1N4148 (fast reset)
D306, D307, D308, D309: 1N4007
J301: T1 12VAC
J302: AMP L OUT -> SPK L+
J303: AMP R OUT -> SPK R+
J304: AMP L JP1 (RUN, VEE)
J305: AMP R JP1 (RUN, VEE)
J306: TO MAINS K_BYP COIL (BYP_HI, GND)
J307: FRONT LED GREEN (A, K)
J308: FRONT LED RED (A, K->RLY)
J309: GND TO PSU STAR (one point)
K301, K302: G2RL-1-E 12VDC
Q301: BC327-40 (PNP, 800 mA)
Q302: BC327-40
R301: 3.3k
R302, R304, R305, R306: 56k
R303, R309, R314: 1k
R307, R308: 10k
R310: 1k GREEN
R311: 1.5k RED
R312: 220k
R313: 2.2k
R315: 1M hysteresis
U301: 7812 (TO-220, to chassis)
U302: UPC1237 SIP-8
U303, U304: SFH617A-3 (Vceo 70 V)
U305: TL431 (2.5 V comparator)

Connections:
+12V: C303.1, C304.1, D305.1 (K), Q301.E, Q302.E, R301.2, R308.2, R311.1, R312.1, R313.2, U301.OUT
ACDET: C307.1, R306.1, R307.1, U302.4 (ACOFF)
ACSENSE: D301.1 (K), R306.2
AC_A: D301.2 (A), D306.2 (A), D308.1 (K), J301.1
AC_B: D307.2 (A), D309.1 (K), J301.2
AMP_L_OUT: J302.1, K301.COM, R304.1
AMP_R_OUT: J303.1, K302.COM, R305.1
BYP_HI: J306.1, Q302.C, R315.2
DCDET: C306.1, R304.2, R305.2, U302.2 (DC)
DELAY: C305.1, R302.1, U302.7 (DELAY)
GND: C301.2, C302.2, C303.2, C304.2, C305.2, C306.2, C307.2, C308.2, D302.2 (A), D303.2 (A), D308.2 (A), D309.2 (A), J306.2, J307.2, J309.1, J309.2, K301.A2, K302.A2, R307.2, U301.GND, U302.1 (OVL), U302.3 (LATCH), U302.5 (GND), U304.K, U305.A
LED_G: J307.1, R310.2
LED_R: J308.1, R311.2
OPTO_A: R309.2, U303.A
OPTO_M: U303.K, U304.A
Q1B: Q301.B, R303.2, R308.1
Q2B: Q302.B, R314.2
RAW: C301.1, C302.1, D306.1 (K), D307.1 (K), U301.IN
RLY: D302.1 (K), D303.1 (K), J308.2, K301.A1, K302.A1, Q301.C, R309.1, R310.1
RLYDRV: R303.1, U302.6 (RLY)
RUN_L: J304.1, U303.C
RUN_R: J305.1, U304.C
SPK_L: J302.2, K301.NO
SPK_R: J303.2, K302.NO
TLK: R313.1, R314.1, U305.K
TMR: C308.1, D305.2 (A), R312.2, R315.1, U305.REF
VEE_L: J304.2, U303.E
VEE_R: J305.2, U304.E
VREF: R301.1, R302.2, U302.8 (VREF)

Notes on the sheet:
CTRL BOARD V0.6 / FIRST CIRCUIT DRAFT 2026-10-01 / UPC1237 protector + 12 V aux + soft-start timer / NO HARDWARE MEASUREMENT
Supply: T1 12 VAC winding (12.27 V no-load measured 2026-10-01, 1 A label) -> bridge -> 2200u -> 7812 -> +12V for relays, logic and UPC1237.
GND of this board ties to the PSU GND star at ONE point (J309). Relay coil current never flows through the amplifier signal ground (docs/13).
A. 12 V AUXILIARY SUPPLY
D306-D309 = full bridge: AC_A/AC_B -> D306/D307 cathodes = RAW; D308/D309 anodes = GND.
RAW ~15-17 VDC at ~120 mA (3 x 33 mA G2RL coils + logic). 7812 dissipates ~0.6 W: clip heatsink or bolt to chassis. Ripple 2200u @120 mA ~0.5 Vpp (docs/14 6.5).
B. UPC1237 PROTECTOR (UTC QW-R107-065.B)
Thresholds: pin 2 +0.62 V / -0.17 V (DC), pin 4 0.74 V (AC-off), pin 8 = 3.4 V reference, pin 6 sinks <= 80 mA.
Pin 1 (overload) and pin 3 grounded: overload detector unused, automatic reset. For LATCH put 22n from pin 3 to GND instead.
DC trip (one channel, other at 0 V): +1.24 V / -0.34 V at the speaker output. 56k||56k x 100u = 2.8 s: 30 V fault trips in ~120 ms; 25 Vpk at 10 Hz leaves 0.07 V at pin 2 (<0.17 V).
AC-off: 17 Vpk x 10k/66k = 2.6 V at pin 4 while mains is on (droop between peaks to 1.8 V); after loss 10k x 4.7u decays below 0.74 V in ~60 ms (docs/14 6.4 budget <60 ms).
C. SPEAKER RELAYS (G2RL-1-E 12VDC, 16 A, 2 x 33 mA), MUTE OPTOS, STATUS LEDS
Speaker return wire goes straight from the binding post to the amplifier J2.2 / J4.2, never through this board (docs/14 4).
Relay DC breaking: G2RL-1-E is rated 30 VDC; a 33.5 V / 8 ohm fault (4.5 A) is a one-shot protective break, accepted 2026-10-01 (docs/14 6.3 asks >=36 VDC).
Opto collector -> amplifier RUN (R8 end), emitter -> that board VEE: closes the JP1 position, 1.3 mA. Two independent paths; the L and R mute nodes stay isolated (docs/13).
Opto must stand |VEE| = 36 V when off: SFH617A-3 (70 V, DIP-4) or H11D1 (300 V, DIP-6); NOT PC817 (35 V). LED chain 2 x 1.2 V at ~8 mA from RLY through R309.
E. FRONT PANEL LEDS: green = speakers ON (from RLY), red = +12V present but relay OFF (returns into RLY)
Red LED returns into RLY: lit while RLY sits low (~6 mA through the coils, far below pull-in), dark once Q301 pulls RLY high.
D. SOFT-START BYPASS TIMER: K_BYP (on MAINS board) pulls in ~1.1 s after +12V (docs/14 6.2 recommends 1 s)
t = 220k x 22u x ln(12/9.5) = 1.1 s. TL431 snaps at 2.5 V (sharp, no relay chatter); R315 adds ~0.3 V hysteresis; D305 empties C308 within ms at power-off so a quick off-on restarts the NTC limit.
Flyback diode for K_BYP sits on the MAINS board next to the coil (D403). K_TRIG is on the MAINS board, powered by the Z10 trigger, not by this board.
NOT DRAWN YET: single-rail-loss detector (docs/13 P5, optional), over-temperature (P6, optional). Component values are first-pass; every timing and threshold is to be measured per docs/14 9 before the board goes into the chassis.

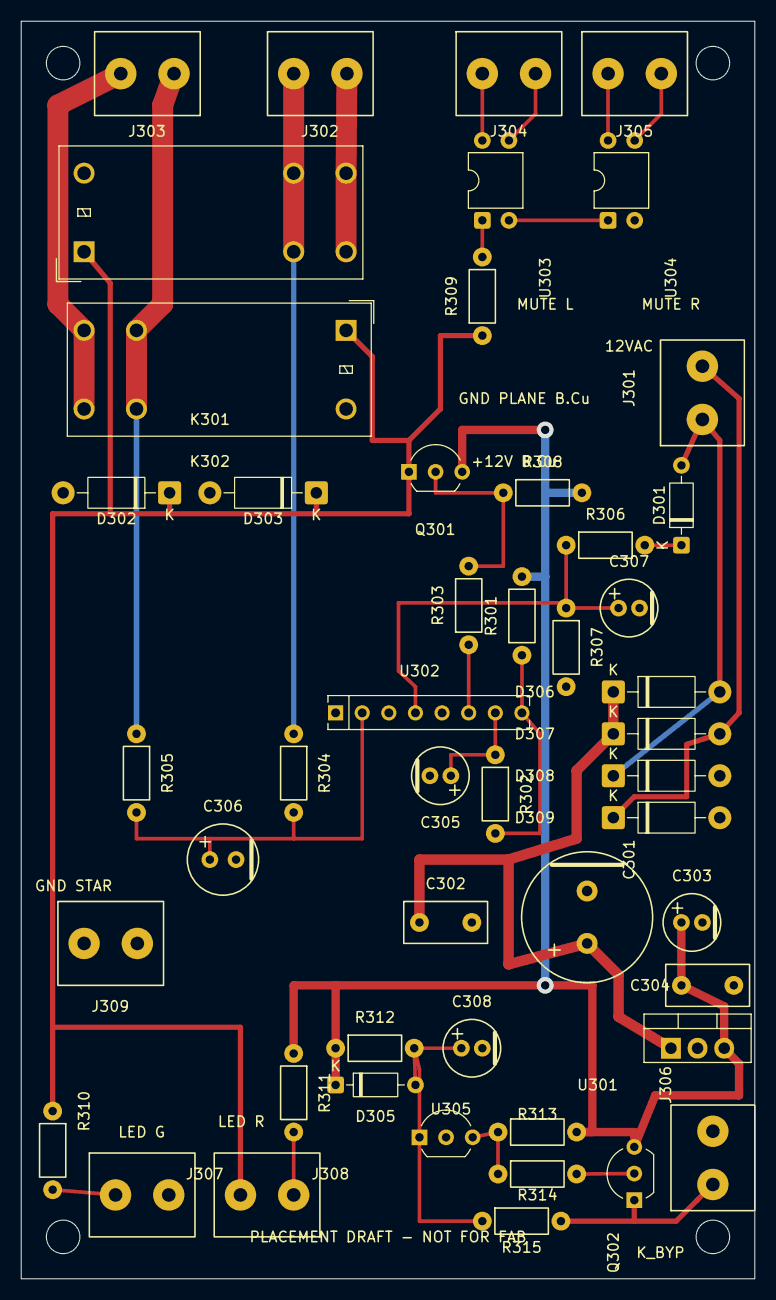
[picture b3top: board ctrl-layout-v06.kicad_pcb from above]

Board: 2 copper layers, 70.0 x 120.0 mm, 53 parts (0 on the bottom side), 29 nets.

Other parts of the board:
H1, H2, H3, H4: M3 provisional

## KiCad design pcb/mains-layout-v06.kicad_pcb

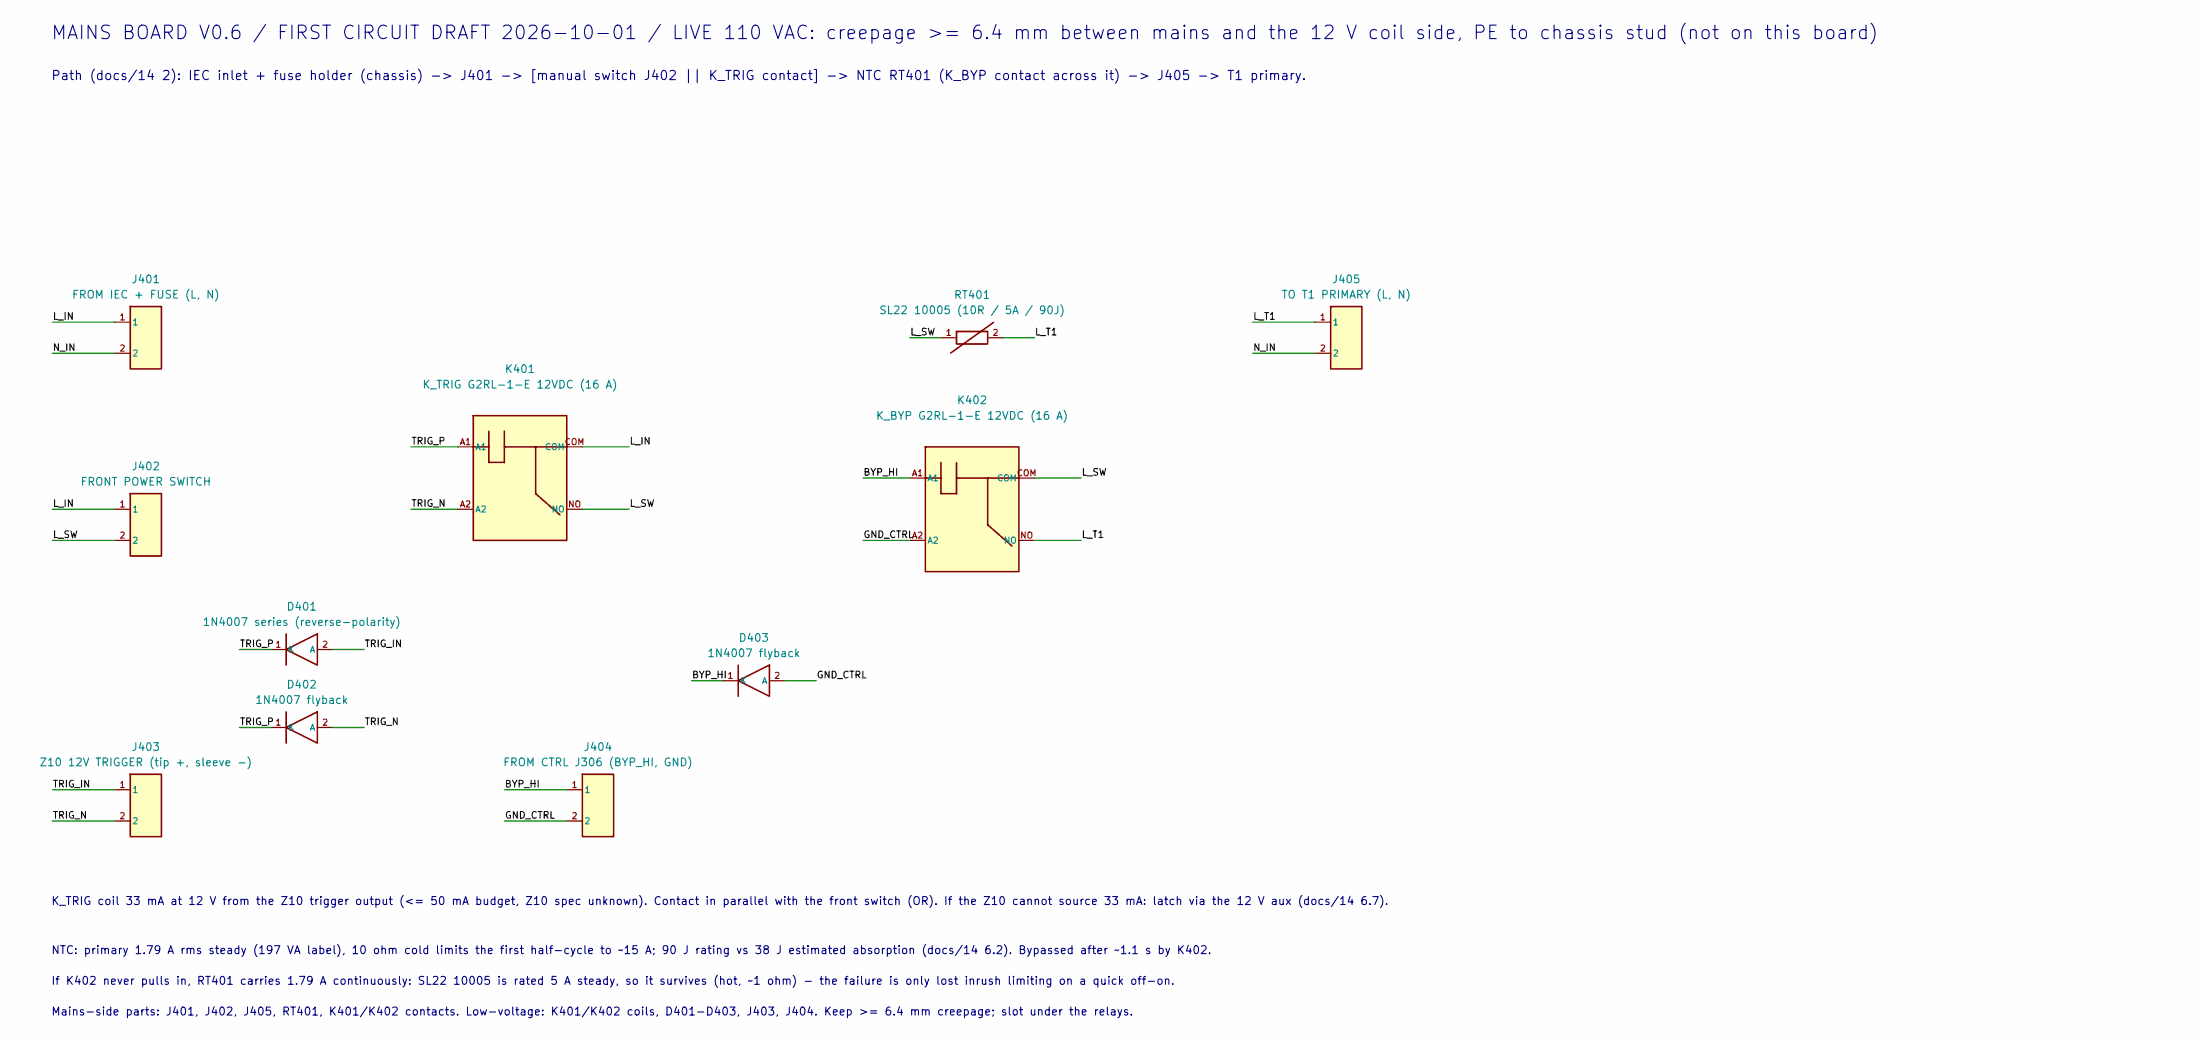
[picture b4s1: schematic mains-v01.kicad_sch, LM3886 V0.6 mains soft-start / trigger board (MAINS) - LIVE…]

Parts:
D401: 1N4007 series (reverse-polarity)
D402, D403: 1N4007 flyback
J401: FROM IEC + FUSE (L, N)
J402: FRONT POWER SWITCH
J403: Z10 12V TRIGGER (tip +, sleeve -)
J404: FROM CTRL J306 (BYP_HI, GND)
J405: TO T1 PRIMARY (L, N)
K401: K_TRIG G2RL-1-E 12VDC (16 A)
K402: K_BYP G2RL-1-E 12VDC (16 A)
RT401: SL22 10005 (10R / 5A / 90J)

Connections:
BYP_HI: D403.1 (K), J404.1, K402.A1
GND_CTRL: D403.2 (A), J404.2, K402.A2
L_IN: J401.1, J402.1, K401.COM
L_SW: J402.2, K401.NO, K402.COM, RT401.1
L_T1: J405.1, K402.NO, RT401.2
N_IN: J401.2, J405.2
TRIG_IN: D401.2 (A), J403.1
TRIG_N: D402.2 (A), J403.2, K401.A2
TRIG_P: D401.1 (K), D402.1 (K), K401.A1

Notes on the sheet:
MAINS BOARD V0.6 / FIRST CIRCUIT DRAFT 2026-10-01 / LIVE 110 VAC: creepage >= 6.4 mm between mains and the 12 V coil side, PE to chassis stud (not on this board)
Path (docs/14 2): IEC inlet + fuse holder (chassis) -> J401 -> [manual switch J402 || K_TRIG contact] -> NTC RT401 (K_BYP contact across it) -> J405 -> T1 primary.
K_TRIG coil 33 mA at 12 V from the Z10 trigger output (<= 50 mA budget, Z10 spec unknown). Contact in parallel with the front switch (OR). If the Z10 cannot source 33 mA: latch via the 12 V aux (docs/14 6.7).
NTC: primary 1.79 A rms steady (197 VA label), 10 ohm cold limits the first half-cycle to ~15 A; 90 J rating vs 38 J estimated absorption (docs/14 6.2). Bypassed after ~1.1 s by K402.
If K402 never pulls in, RT401 carries 1.79 A continuously: SL22 10005 is rated 5 A steady, so it survives (hot, ~1 ohm) - the failure is only lost inrush limiting on a quick off-on.
Mains-side parts: J401, J402, J405, RT401, K401/K402 contacts. Low-voltage: K401/K402 coils, D401-D403, J403, J404. Keep >= 6.4 mm creepage; slot under the relays.

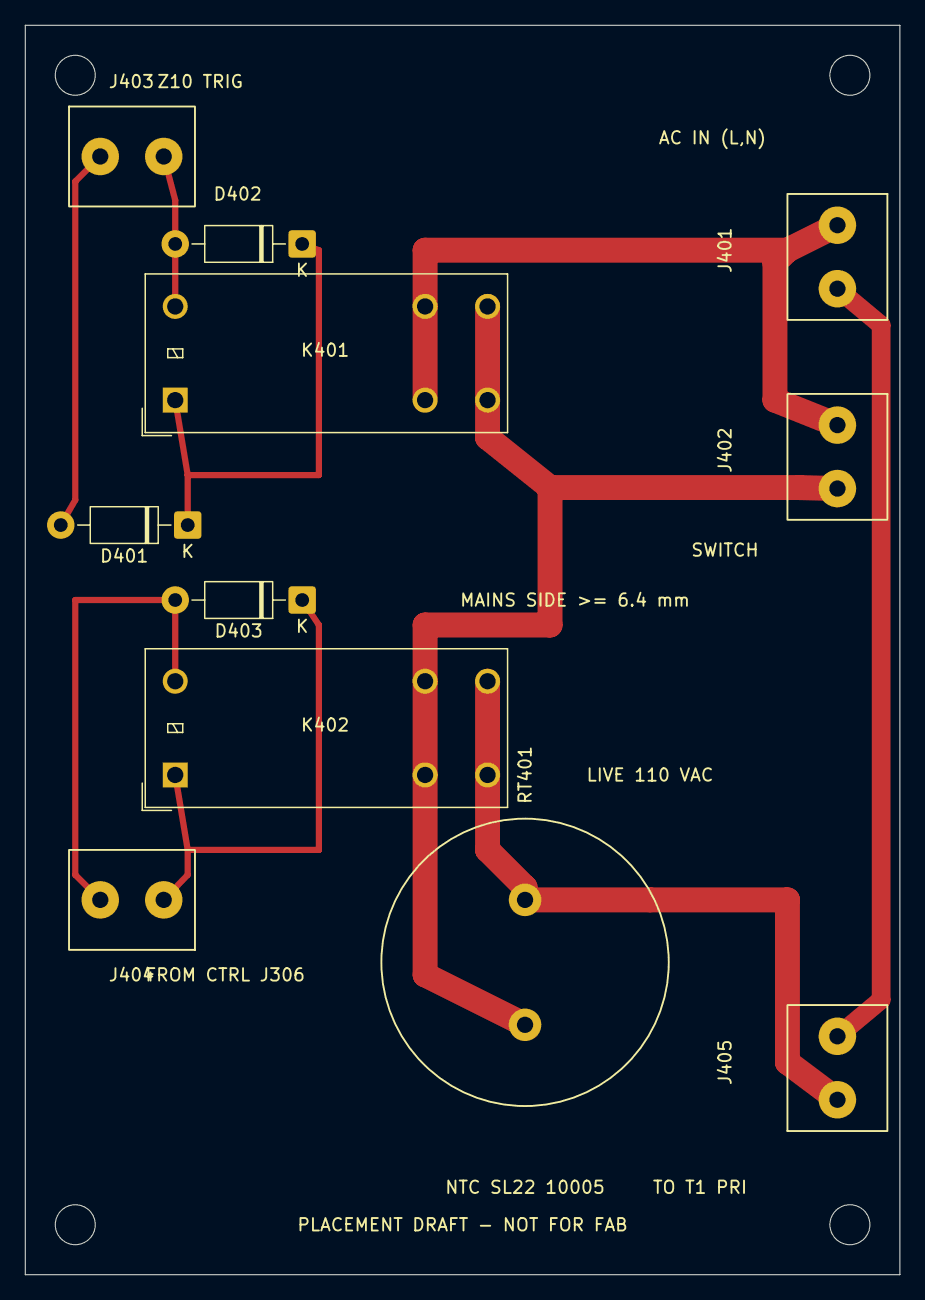
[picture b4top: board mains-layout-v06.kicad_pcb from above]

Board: 2 copper layers, 70.0 x 100.0 mm, 15 parts (0 on the bottom side), 9 nets.

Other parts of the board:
H1, H2, H3, H4: M3 provisional

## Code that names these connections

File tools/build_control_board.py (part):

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    d.wire(d.pin('U302', 8), d.pin('R301', 1))
    d.label(*d.pin('U302', 8), 'VREF')
    d.terminal('R301', 2, '+12V', dx=5.08)
    # delay: 56k from VREF to pin 7, 47u to GND -> relay ON ~3-4 s after VREF appears (datasheet 56k/33u ~2-3 s); trim on the bench
    d.part('R', 'R302', '56k', 165.1, y - 2.54)
    d.wire(d.pin('U302', 7), d.pin('R302', 1))
    d.terminal('R302', 2, 'VREF', dx=5.08)
    d.part('CP', 'C305', '47u / 16V DELAY', 165.1, y + 10.16)
    d.terminal('C305', 1, 'DELAY', dx=-5.08)
    d.label(*d.pin('U302', 7), 'DELAY')
    d.terminal('C305', 2, 'GND', dx=5.08)
    # relay driver: pin 6 sinks the PNP base current; R303 limits it to ~10 mA
    d.part('R', 'R303', '1k', 139.7, y + 2.54)
    d.wire(d.pin('U302', 6), d.pin('R303', 1))
    d.label(*d.pin('U302', 6), 'RLYDRV')
    d.terminal('R303', 2, 'Q1B', dx=5.08)
    d.terminal('U302', 5, 'GND', dy=5.08)
    d.terminal('U302', 1, 'GND', dx=-5.08)     # overload detector unused -> grounded (test-circuit SW1 position 2)
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    d.part('R', 'R305', '56k', 55.88, y + 7.62)
    d.terminal('R305', 1, 'AMP_R_OUT', dx=-5.08)
    d.terminal('R305', 2, 'DCDET', dx=5.08)
    d.label(*d.pin('U302', 2), 'DCDET')
    d.part('CP', 'C306', '100u / 16V (datasheet 330u)', 55.88, y + 17.78)
    d.terminal('C306', 1, 'DCDET', dx=-5.08)
    d.terminal('C306', 2, 'GND', dx=5.08)
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    d.terminal('D301', 2, 'AC_A', dx=5.08)
    d.part('R', 'R306', '56k', 40.64, y - 22.86)
    d.wire(d.pin('D301', 1), d.pin('R306', 2))
    d.label(*d.pin('D301', 1), 'ACSENSE')
    d.terminal('R306', 1, 'ACDET', dx=-5.08)
    d.part('R', 'R307', '10k', 40.64, y - 12.7)
    d.terminal('R307', 1, 'ACDET', dx=-5.08)
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        d.terminal(j, 1, 'RUN_%s' % ch, dx=-7.62)
        d.terminal(j, 2, 'VEE_%s' % ch, dx=-7.62)
    d.text(x - 20, yy + 14, 'Opto collector -> amplifier RUN (R8 end), emitter -> that board VEE: closes the JP1 position, 1.3 mA. Two independent paths; the L and R mute nodes stay isolated (docs/13).', 1.3)
    d.text(x - 20, yy + 19, 'Opto must stand |VEE| = 36 V when off: SFH617A-3 (70 V, DIP-4) or H11D1 (300 V, DIP-6); NOT PC817 (35 V). LED chain 2 x 1.2 V at ~8 mA from RLY through R309.', 1.3)
    # status LEDs on the front panel: green = relay ON (from RLY), red = +12V present but relay OFF (returns into RLY node)
    # front-panel LEDs live in the lower-left block, under the timer (sheet space)
    yy = 262
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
